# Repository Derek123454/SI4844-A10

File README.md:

# SI4844-A10
Radio project based on Si4844-A10
Original Source https://www.allaboutcircuits.com/projects/build-an-arduino-controlled-am-fm-sw-radio/
Arduino board files are an arduino pro mini and a dual lm386 op amp to be combined with the original Si4484-A10 board file

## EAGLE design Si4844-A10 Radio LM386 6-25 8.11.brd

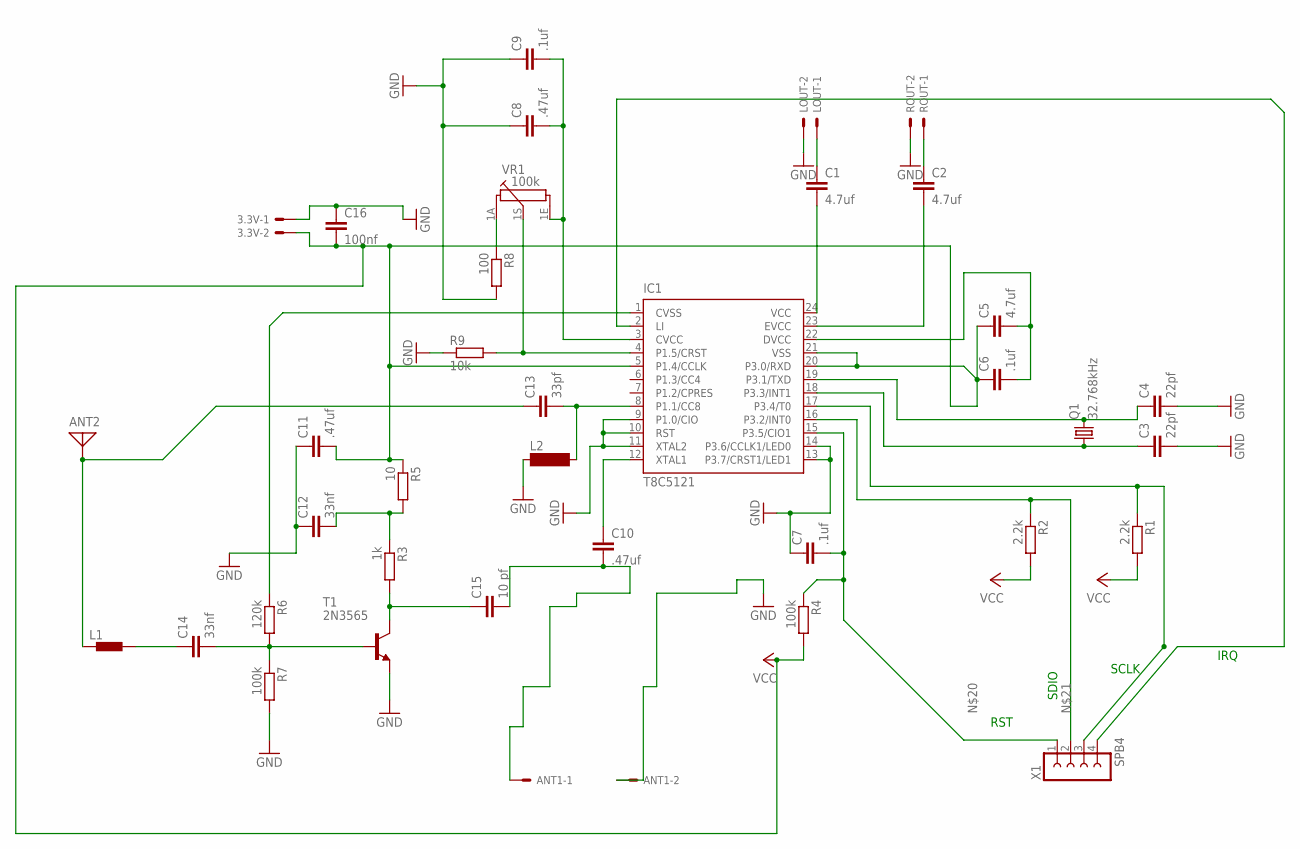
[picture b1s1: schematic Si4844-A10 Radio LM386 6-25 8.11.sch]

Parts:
3.3V: 22-23-2021
ANT1: 332-02
ANT2: ANTENNA; PAD-01
C1, C2, C5: 4.7uf; C2.5-2
C3, C4: 22pf; C2.5-2
C6, C7, C9: .1uf; C2.5-2
C8, C10: .47uf; C2.5-2
C11: .47uf; C2.5-3
C12, C14: 33nf; C2.5-3
C13: 33pf; C2.5-3
C15: 10 pf; C2.5-3
C16: 100nf; C2.5-2
IC1: T8C5121; SSOP24
L1: BLM15HB121SN1; 0402
L2: SM-1206
LOUT: 22-23-2021
Q1: 32.768kHz; TC26V
R1, R2: 2.2k; 0204/7
R3: 1k; 0204/7
R4, R7: 100k; 0204/7
R5: 10; 0204/7
R6: 120k; 0204/7
R8: 100; 0204/7
R9: 10k; 0204/7
ROUT: 22-23-2021
T1: 2N3565; TO92
VR1: 100k; PC16S
X1: SPB4

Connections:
GND: 3.3V.1, ANT1.2, C3.2, C4.2, C7.1, C8.1, C9.1, C11.1, C12.1, C16.1, IC1.9 (P1.0/CIO), IC1.10 (RST), IC1.11 (XTAL2), IC1.13 (P3.7/CRST1/LED1), IC1.14 (P3.6/CCLK1/LED0), L2.1, LOUT.2, R7.2, R8.2, R9.1, ROUT.2, T1.3 (E)
unnamed: C10.1, IC1.12 (XTAL1)
unnamed: C13.2, IC1.8 (P1.1/CC8), L2.2
unnamed: C15.1, R3.2, T1.1 (C)
unnamed: C12.2, R3.1, R5.2
unnamed: IC1.17 (P3.4/T0), R1.1, X1.3
unnamed: C14.2, R6.2, R7.1, T1.2 (B)
unnamed: C14.1, L1.2
unnamed: ANT2.1, C13.1, L1.1
unnamed: IC1.4 (P1.5/CRST), R9.2, VR1.1S
unnamed: IC1.1 (CVSS), R6.1
unnamed: C1.2, IC1.24 (VCC)
unnamed: C8.2, C9.2, IC1.3 (CVCC), VR1.1E
unnamed: C2.2, IC1.23 (EVCC)
unnamed: C1.1, LOUT.1
unnamed: R8.1, VR1.1A
unnamed: C2.1, ROUT.1
unnamed: C5.2, C6.2, IC1.22 (DVCC)
unnamed: C4.1, IC1.19 (P3.1/TXD), Q1.2
unnamed: C3.1, IC1.18 (P3.3/INT1), Q1.1
unnamed: C7.2, IC1.15 (P3.5/CIO1), R4.1, X1.1
unnamed: IC1.16 (P3.2/INT0), R2.1, X1.2
unnamed: IC1.2 (LI), X1.4
unnamed: ANT1.1, C10.2, C15.2
VCC: 3.3V.2, C5.1, C6.1, C11.2, C16.2, IC1.5 (P1.4/CCLK), IC1.20 (P3.0/RXD), IC1.21 (VSS), R1.2, R2.2, R4.2, R5.1

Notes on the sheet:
RST
SDIO
SCLK
IRQ

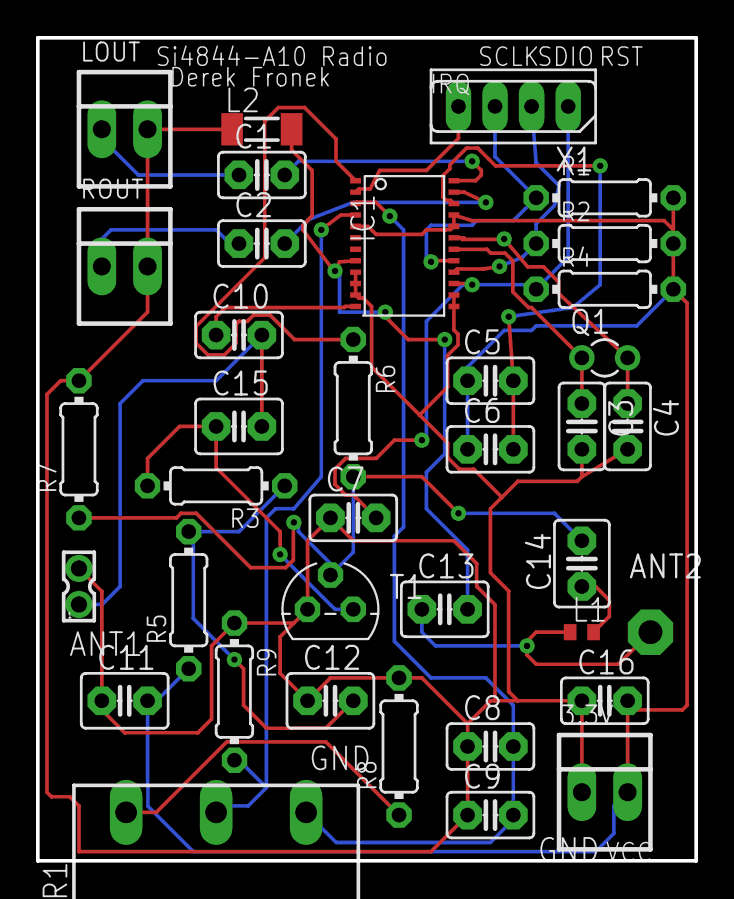
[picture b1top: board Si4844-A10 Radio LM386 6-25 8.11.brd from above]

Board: 2 copper layers, 36.6 x 45.7 mm, 37 parts (0 on the bottom side), 25 nets.

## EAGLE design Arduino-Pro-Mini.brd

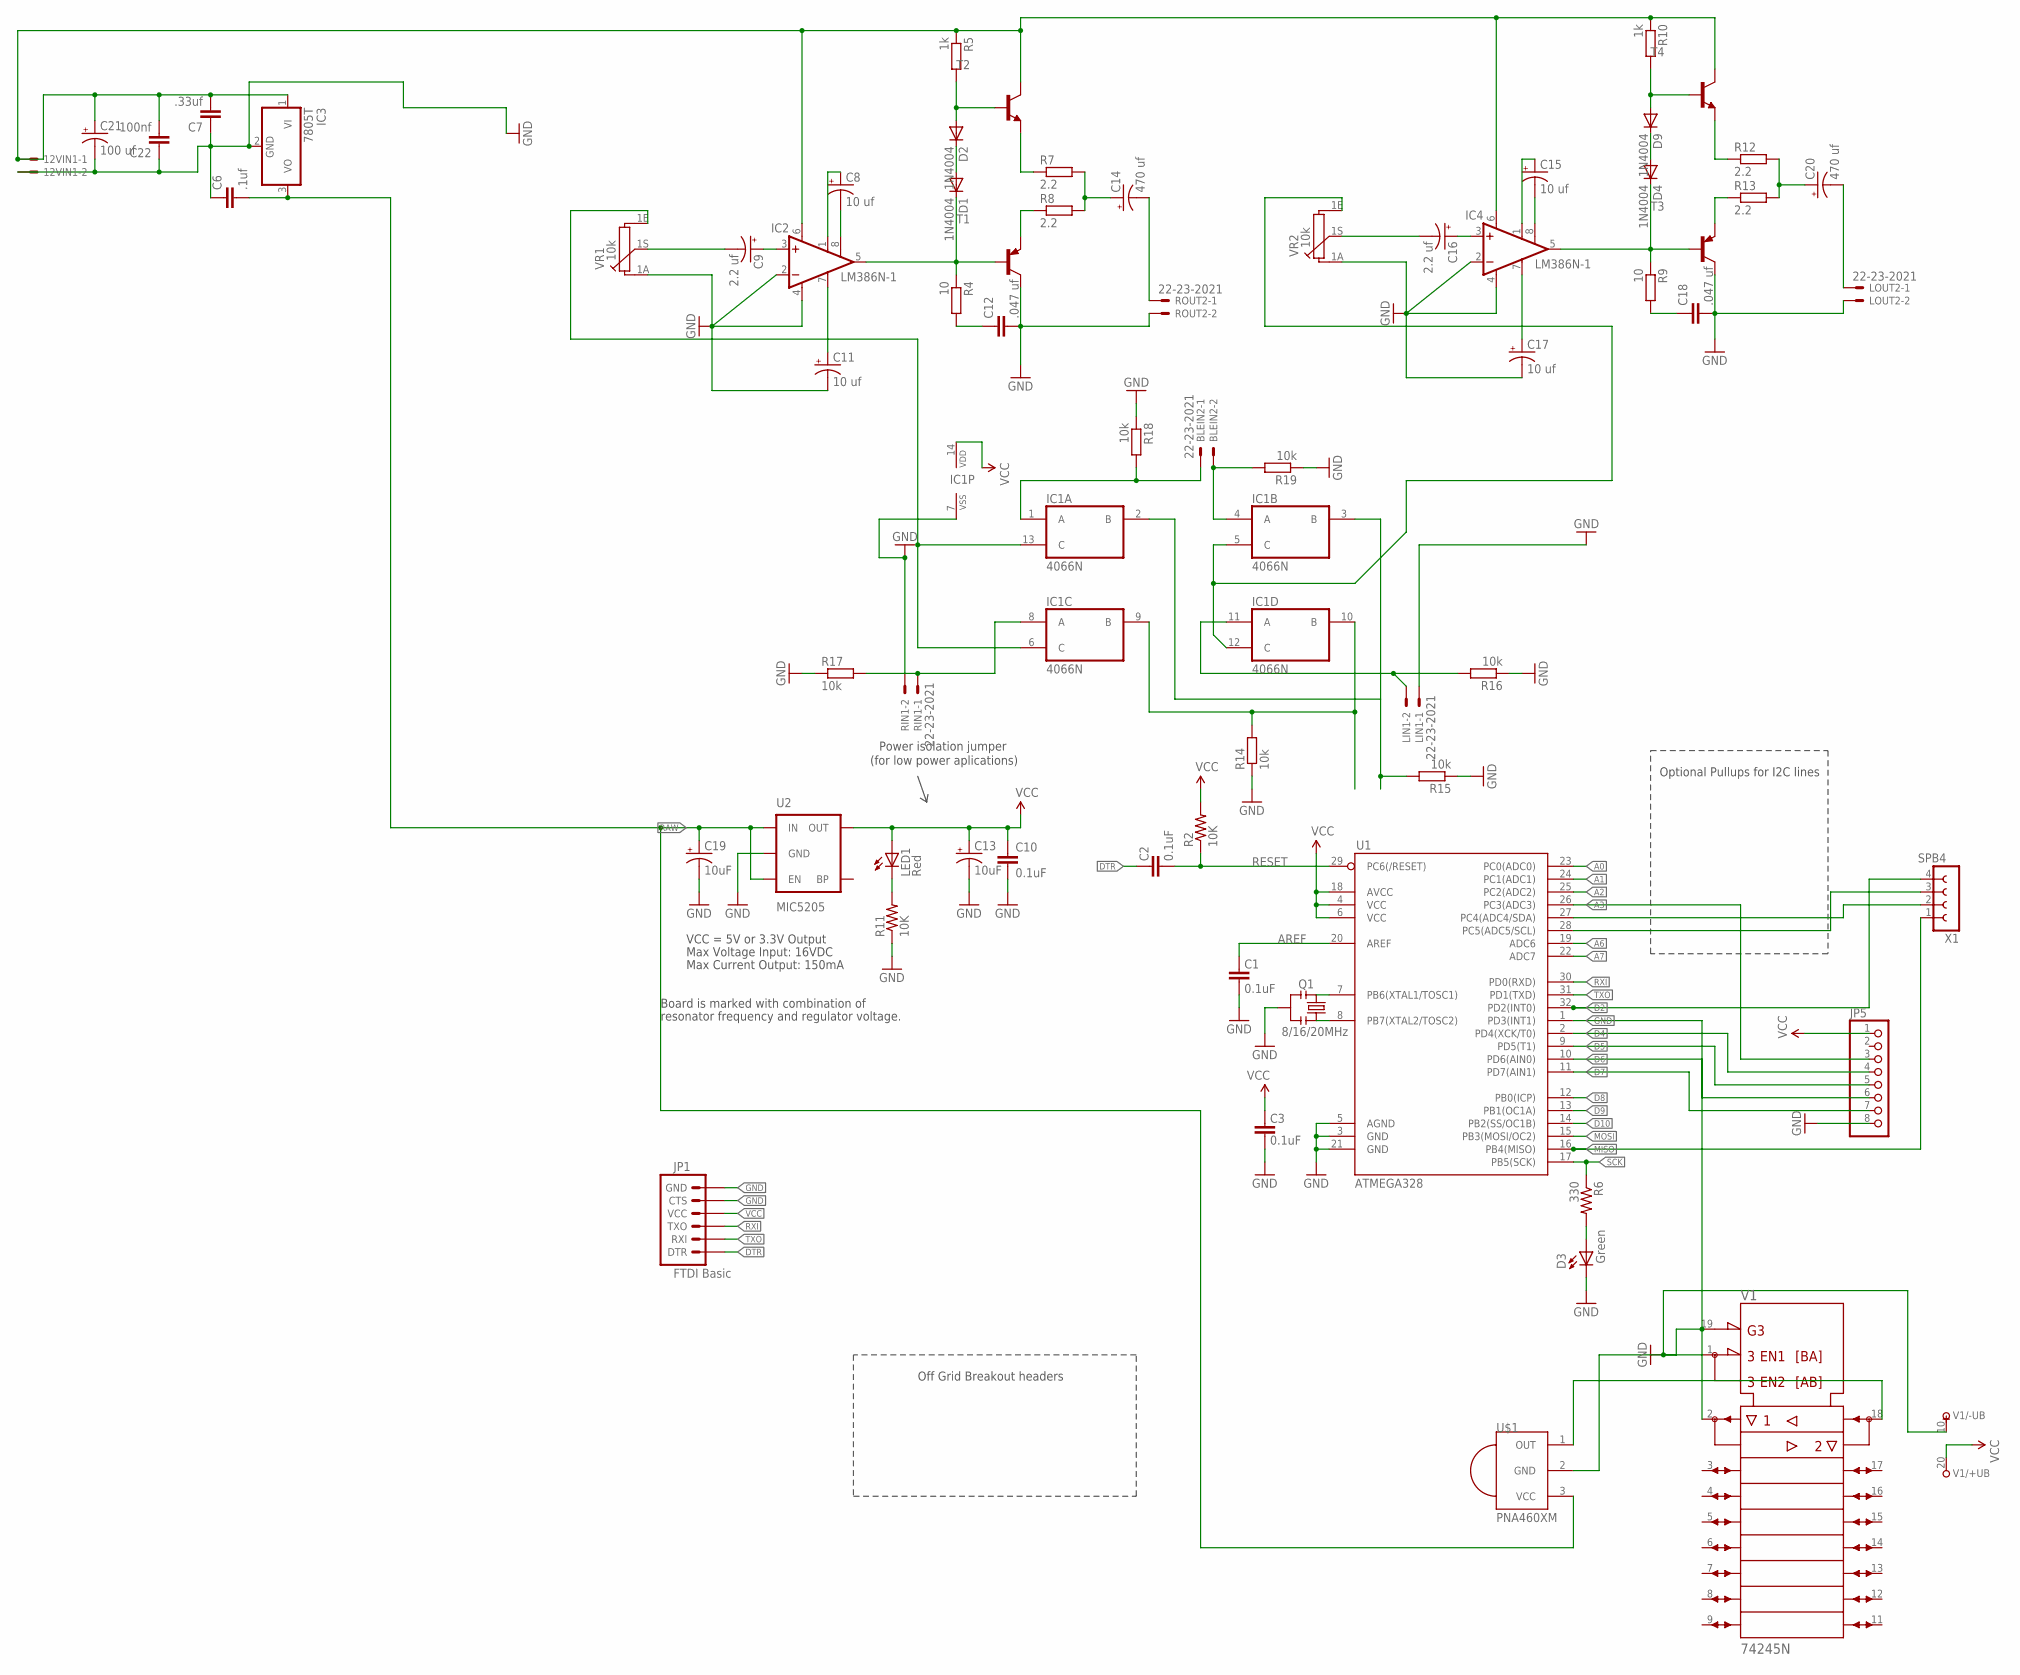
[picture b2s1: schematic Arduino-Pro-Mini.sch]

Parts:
12VIN1: 22-23-2021
BLEIN2: 22-23-2021
C1, C2, C3, C10: 0.1uF; CAP-PTH-5MM
C6: .1uf; C2.5-2
C7: .33uf; C2.5-2
C8, C11, C15, C17: 10 uf; E1,8-4
C9, C16: 2.2 uf; E1,8-4
C12, C18: .047 uf; C2.5-2
C13, C19: 10uF; CPOL-RADIAL-100UF-25V
C14, C20: 470 uf; E2,5-6E
C21: 100 uf; E1,8-4
C22: 100nf; C2.5-2
D1, D2, D4, D9: 1N4004; DO41-10
D3: Green; LED5MM
IC1: 4066N; DIL14
IC2, IC4: LM386N-1; DIL08
IC3: 7805T; TO220H
JP1: FTDI Basic; 1X06
JP5: PINHD-1X8BIG; 1X08-BIG
LED1: Red; LED5MM
LIN1: 22-23-2021
LOUT2: 22-23-2021
Q1: 8/16/20MHz; RESONATOR-PTH
R2, R11: 10K; AXIAL-0.3
R4, R9: 10; 0204/7
R5, R10: 1k; 0204/7
R6: 330; AXIAL-0.3
R7, R8, R12, R13: 2.2; 0204/7
R14, R15, R16, R17, R18, R19: 10k; 0204/7
RIN1: 22-23-2021
ROUT2: 22-23-2021
T1, T3: -PNP-TO92; TO92
T2, T4: -NPN-TO92; TO92
U1: ATMEGA328; TQFP32-08
U2: MIC5205; SOT23-5
U$1: PNA460XM
V1: 74245N; DIL20
VR1, VR2: 10k; PC16S
X1: SPB4

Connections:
3.3V: IC1.14 (VDD), JP5.1, V1.20 (+UB)
A0: U1.23 (PC0(ADC0))
A1: U1.24 (PC1(ADC1))
A2: U1.25 (PC2(ADC2))
A3: JP5.3, U1.26 (PC3(ADC3))
A4: U1.27 (PC4(ADC4/SDA)), X1.2
A5: U1.28 (PC5(ADC5/SCL)), X1.3
A6: U1.19 (ADC6)
A7: U1.22 (ADC7)
AREF: C1.2, U1.20 (AREF)
D2: U1.32 (PD2(INT0)), X1.4
D4: JP5.4, U1.2 (PD4(XCK/T0))
D5: JP5.5, U1.9 (PD5(T1))
D6: JP5.6, U1.10 (PD6(AIN0))
D7: JP5.7, U1.11 (PD7(AIN1))
D8: U1.12 (PB0(ICP))
D9: U1.13 (PB1(OC1A))
D10: U1.14 (PB2(SS/OC1B))
DTR: C2.2, JP1.1 (DTR)
GND: 12VIN1.2, C1.1, C3.1, C6.1, C7.1, C10.2, C11.-, C12.2, C13.2 (-), C17.-, C18.2, C19.2 (-), C21.-, C22.1, D3.K (C), IC1.7 (VSS), IC2.2 (-IN), IC2.4 (GND), IC3.2 (GND), IC4.2 (-IN), IC4.4 (GND), JP1.5 (CTS), JP1.6 (GND), JP5.8, LIN1.1, LOUT2.2, Q1.2, R11.P$1 (1), R14.1, R15.1, R16.1, R17.1, R18.1, R19.1, RIN1.2, ROUT2.2, T1.3 (C), T3.3 (C), U1.1 (PD3(INT1)), U1.3 (GND), U1.5 (AGND), U1.21 (GND), U2.2 (GND), U$1.2 (GND), V1.1 (DIR), V1.2 (A1), V1.10 (-UB), VR1.1A, VR2.1A
MISO: U1.16 (PB4(MISO)), X1.1
MOSI: U1.15 (PB3(MOSI/OC2))
unnamed: Q1.3, U1.8 (PB7(XTAL2/TOSC2))
unnamed: Q1.1, U1.7 (PB6(XTAL1/TOSC1))
unnamed: LED1.K (C), R11.P$2 (2)
unnamed: BLEIN2.2, IC1.4 (A), R19.2
unnamed: IC1.6 (C), IC1.13 (C), VR1.1E
unnamed: D3.A, R6.P$2 (2)
unnamed: C8.-, IC2.8 (GAIN)
unnamed: C8.+, IC2.1 (GAIN)
unnamed: C9.+, IC2.3 (+IN)
unnamed: C9.-, VR1.1S
unnamed: C11.+, IC2.7 (BYPASS)
unnamed: D1.C, IC2.5 (OUT), R4.1, T1.2 (B)
unnamed: C12.1, R4.2
unnamed: D1.A, D2.C
unnamed: D2.A, R5.2, T2.2 (B)
unnamed: R8.1, T1.1 (E)
unnamed: R7.1, T2.1 (E)
unnamed: C14.+, R7.2, R8.2
unnamed: C14.-, ROUT2.1
unnamed: 12VIN1.1, C7.2, C21.+, C22.2, IC2.6 (VS), IC3.1 (VI), IC4.6 (VS), R5.1, R10.1, T2.3 (C), T4.3 (C)
unnamed: C15.-, IC4.8 (GAIN)
unnamed: C15.+, IC4.1 (GAIN)
unnamed: C16.+, IC4.3 (+IN)
unnamed: C16.-, VR2.1S
unnamed: C17.+, IC4.7 (BYPASS)
unnamed: D4.C, IC4.5 (OUT), R9.1, T3.2 (B)
unnamed: C18.1, R9.2
unnamed: D4.A, D9.C
unnamed: D9.A, R10.2, T4.2 (B)
unnamed: R13.1, T3.1 (E)
unnamed: R12.1, T4.1 (E)
unnamed: C20.+, R12.2, R13.2
unnamed: IC1.8 (A), R17.2, RIN1.1
unnamed: C20.-, LOUT2.1
unnamed: IC1.5 (C), IC1.12 (C), VR2.1E
unnamed: BLEIN2.1, IC1.1 (A), R18.2
unnamed: IC1.11 (A), LIN1.2, R16.2
unnamed: U$1.1 (OUT), V1.18 (B1)
unnamed: IC1.9 (B), IC1.10 (B), R14.2
unnamed: IC1.2 (B), IC1.3 (B), R15.2
RAW: C6.2, C19.1 (+), IC3.3 (VO), U2.1 (IN), U2.3 (EN), U$1.3 (VCC)
RESET: C2.1, R2.P$1 (1), U1.29 (PC6(/RESET))
RXI: JP1.3 (TXO), U1.30 (PD0(RXD))
SCK: R6.P$1 (1), U1.17 (PB5(SCK))
TXO: JP1.2 (RXI), U1.31 (PD1(TXD))
VCC: C3.2, C10.1, C13.1 (+), JP1.4 (VCC), LED1.A, R2.P$2 (2), U1.4 (VCC), U1.6 (VCC), U1.18 (AVCC), U2.5 (OUT)

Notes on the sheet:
Max Voltage Input: 16VDC
Max Current Output: 150mA
Board is marked with combination of
resonator frequency and regulator voltage.
VCC = 5V or 3.3V Output
Optional Pullups for I2C lines
Off Grid Breakout headers
Power isolation jumper
(for low power aplications)

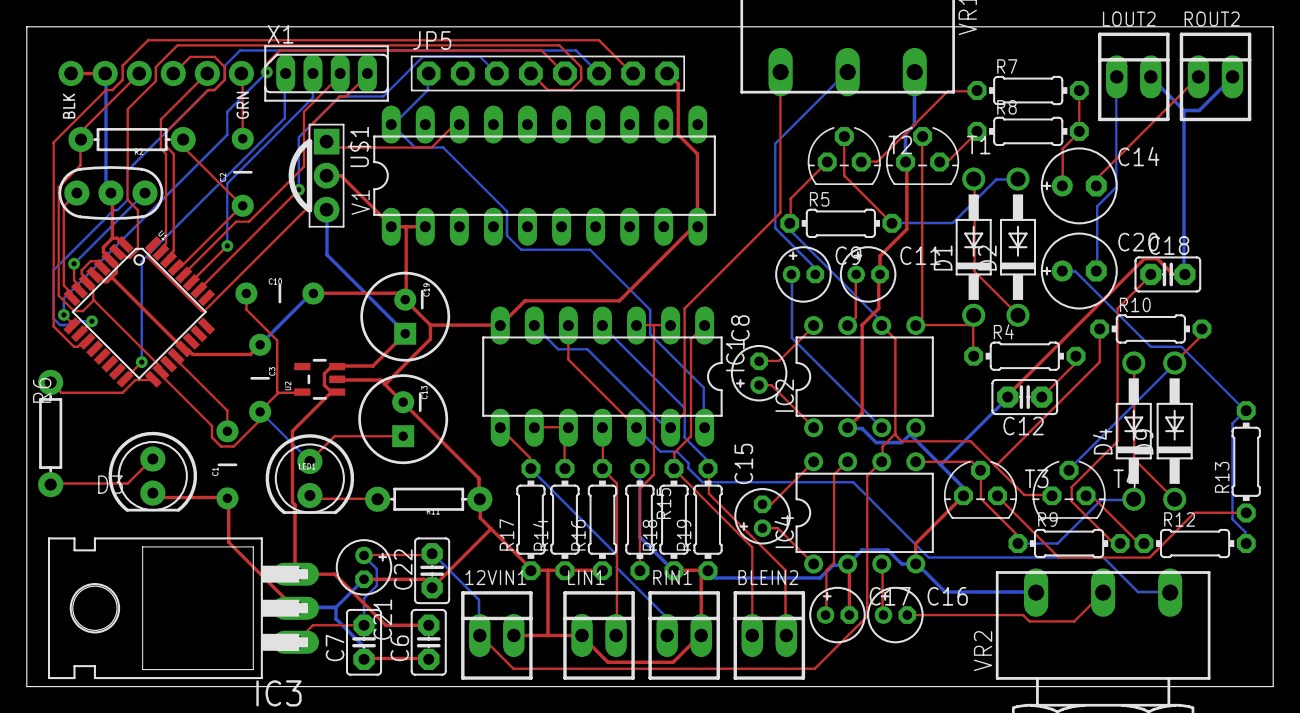
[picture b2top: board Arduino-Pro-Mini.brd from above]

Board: 2 copper layers, 92.9 x 49.2 mm, 67 parts (1 on the bottom side), 59 nets.
